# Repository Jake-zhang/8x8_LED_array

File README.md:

# 8x8_LED_array
8x8 led array kicad project

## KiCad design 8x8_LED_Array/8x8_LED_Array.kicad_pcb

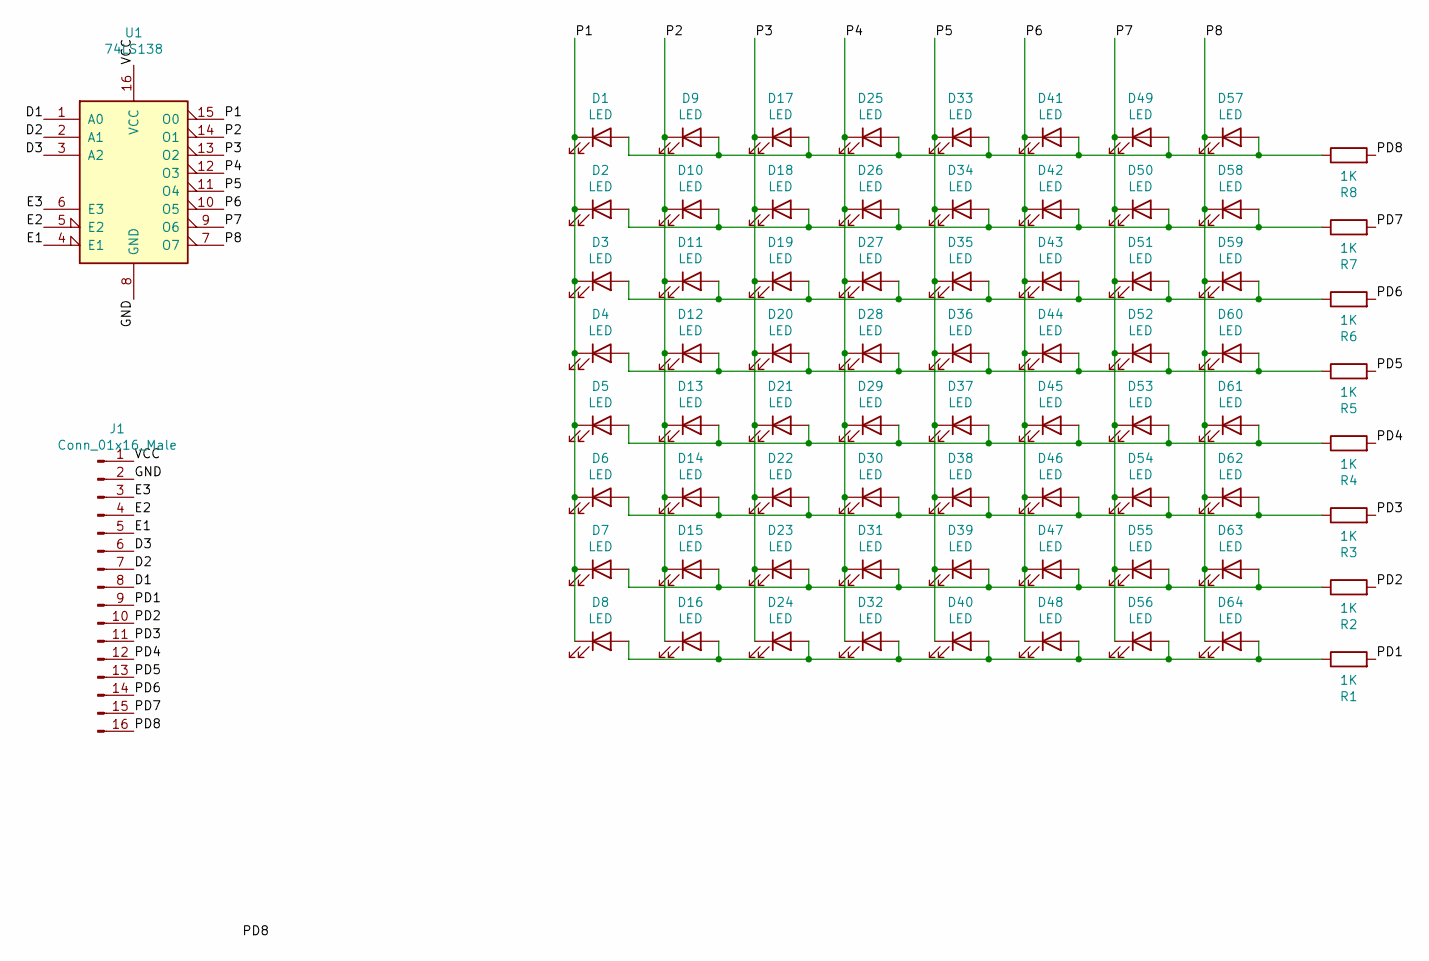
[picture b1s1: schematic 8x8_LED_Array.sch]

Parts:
D1, D2, D3, D4, D5, D6, D7, D8, D9, D10, D11, D12, D13, D14, D15, D16, D17, D18, D19, D20, D21, D22, D23, D24, D25, D26, D27, D28, D29, D30, D31, D32, D33, D34, D35, D36, D37, D38, D39, D40, D41, D42, D43, D44, D45, D46, D47, D48, D49, D50, D51, D52, D53, D54, D55, D56, D57, D58, D59, D60, D61, D62, D63, D64: LED; LED_0805_2012Metric_Pad1.15x1.40mm_HandSolder
J1: Conn_01x16_Male; PinHeader_1x16_P2.54mm_Horizontal
R1, R2, R3, R4, R5, R6, R7, R8: 1K; R_0805_2012Metric_Pad1.15x1.40mm_HandSolder
U1: 74LS138; SOP-16_4.55x10.3mm_P1.27mm

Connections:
/D1: J1.8, U1.1 (A0)
/D2: J1.7, U1.2 (A1)
/D3: J1.6, U1.3 (A2)
/E1: J1.5, U1.4 (E1)
/E2: J1.4, U1.5 (E2)
/E3: J1.3, U1.6 (E3)
/GND: J1.2, U1.8 (GND)
/P1: D1.1 (K), D2.1 (K), D3.1 (K), D4.1 (K), D5.1 (K), D6.1 (K), D7.1 (K), D8.1 (K), U1.15 (O0)
/P2: D9.1 (K), D10.1 (K), D11.1 (K), D12.1 (K), D13.1 (K), D14.1 (K), D15.1 (K), D16.1 (K), U1.14 (O1)
/P3: D17.1 (K), D18.1 (K), D19.1 (K), D20.1 (K), D21.1 (K), D22.1 (K), D23.1 (K), D24.1 (K), U1.13 (O2)
/P4: D25.1 (K), D26.1 (K), D27.1 (K), D28.1 (K), D29.1 (K), D30.1 (K), D31.1 (K), D32.1 (K), U1.12 (O3)
/P5: D33.1 (K), D34.1 (K), D35.1 (K), D36.1 (K), D37.1 (K), D38.1 (K), D39.1 (K), D40.1 (K), U1.11 (O4)
/P6: D41.1 (K), D42.1 (K), D43.1 (K), D44.1 (K), D45.1 (K), D46.1 (K), D47.1 (K), D48.1 (K), U1.10 (O5)
/P7: D49.1 (K), D50.1 (K), D51.1 (K), D52.1 (K), D53.1 (K), D54.1 (K), D55.1 (K), D56.1 (K), U1.9 (O6)
/P8: D57.1 (K), D58.1 (K), D59.1 (K), D60.1 (K), D61.1 (K), D62.1 (K), D63.1 (K), D64.1 (K), U1.7 (O7)
/PD1: J1.9, R1.2
/PD2: J1.10, R2.2
/PD3: J1.11, R3.2
/PD4: J1.12, R4.2
/PD5: J1.13, R5.2
/PD6: J1.14, R6.2
/PD7: J1.15, R7.2
/PD8: J1.16, R8.2
/VCC: J1.1, U1.16 (VCC)
unnamed: D1.2 (A), D9.2 (A), D17.2 (A), D25.2 (A), D33.2 (A), D41.2 (A), D49.2 (A), D57.2 (A), R8.1
unnamed: D2.2 (A), D10.2 (A), D18.2 (A), D26.2 (A), D34.2 (A), D42.2 (A), D50.2 (A), D58.2 (A), R7.1
unnamed: D3.2 (A), D11.2 (A), D19.2 (A), D27.2 (A), D35.2 (A), D43.2 (A), D51.2 (A), D59.2 (A), R6.1
unnamed: D4.2 (A), D12.2 (A), D20.2 (A), D28.2 (A), D36.2 (A), D44.2 (A), D52.2 (A), D60.2 (A), R5.1
unnamed: D5.2 (A), D13.2 (A), D21.2 (A), D29.2 (A), D37.2 (A), D45.2 (A), D53.2 (A), D61.2 (A), R4.1
unnamed: D6.2 (A), D14.2 (A), D22.2 (A), D30.2 (A), D38.2 (A), D46.2 (A), D54.2 (A), D62.2 (A), R3.1
unnamed: D7.2 (A), D15.2 (A), D23.2 (A), D31.2 (A), D39.2 (A), D47.2 (A), D55.2 (A), D63.2 (A), R2.1
unnamed: D8.2 (A), D16.2 (A), D24.2 (A), D32.2 (A), D40.2 (A), D48.2 (A), D56.2 (A), D64.2 (A), R1.1

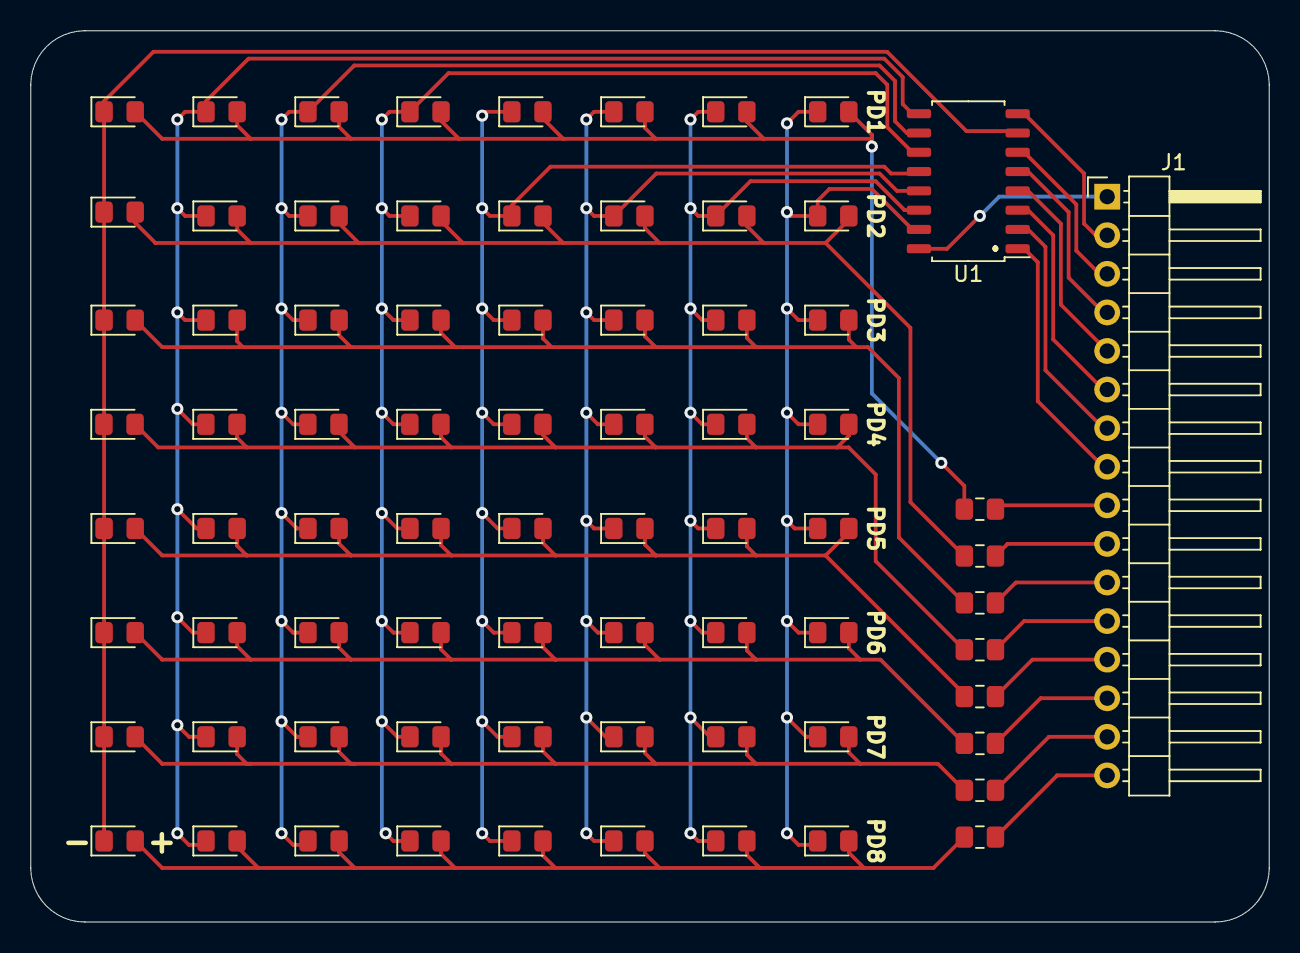
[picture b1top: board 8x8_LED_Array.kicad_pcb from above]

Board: 2 copper layers, 81.5 x 58.7 mm, 74 parts (0 on the bottom side), 32 nets.
